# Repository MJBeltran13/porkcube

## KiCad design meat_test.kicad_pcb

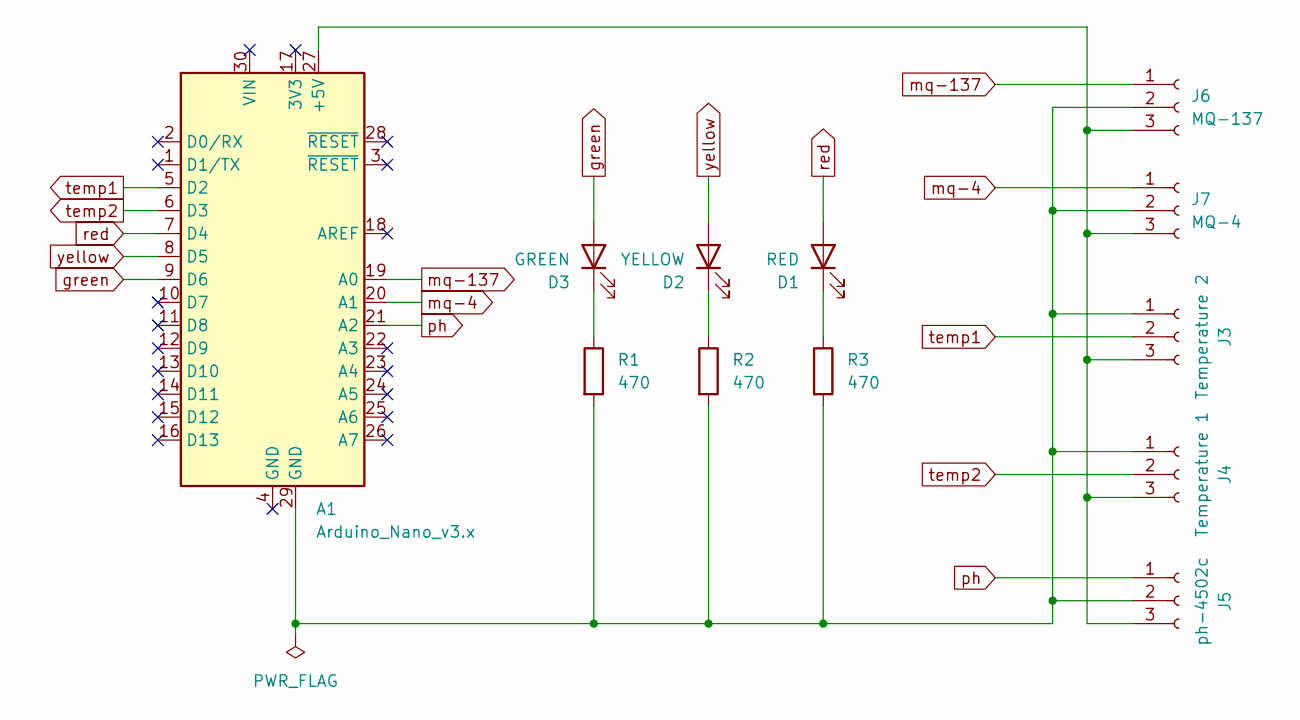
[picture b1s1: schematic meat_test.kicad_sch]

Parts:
A1: Arduino_Nano_v3.x; Arduino_Nano
D1: RED; LED_Rectangular_W3.9mm_H1.8mm_FlatTop
D2: YELLOW; LED_Rectangular_W3.9mm_H1.8mm_FlatTop
D3: GREEN; LED_Rectangular_W3.9mm_H1.8mm_FlatTop
J3: Temperature 2; PinHeader_1x03_P2.54mm_Vertical
J4: Temperature 1; PinHeader_1x03_P2.54mm_Vertical
J5: ph-4502c; PinHeader_1x03_P2.54mm_Vertical
J6: MQ-137; PinHeader_1x03_P2.54mm_Vertical
J7: MQ-4; PinHeader_1x03_P2.54mm_Vertical
R1, R2, R3: 470; R_Axial_DIN0207_L6.3mm_D2.5mm_P10.16mm_Horizontal

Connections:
unnamed: A1.27 (+5V), J3.3, J4.3, J5.3, J6.3, J7.3
unnamed: D1.1 (K), R3.1
unnamed: D2.1 (K), R2.1
unnamed: D3.1 (K), R1.1
unnamed: A1.29 (GND), J3.1, J4.1, J5.2, J6.2, J7.2, R1.2, R2.2, R3.2
green: A1.9 (D6), D3.2 (A)
mq-4: A1.20 (A1), J7.1
mq-137: A1.19 (A0), J6.1
ph: A1.21 (A2), J5.1
red: A1.7 (D4), D1.2 (A)
temp1: A1.5 (D2), J3.2
temp2: A1.6 (D3), J4.2
yellow: A1.8 (D5), D2.2 (A)

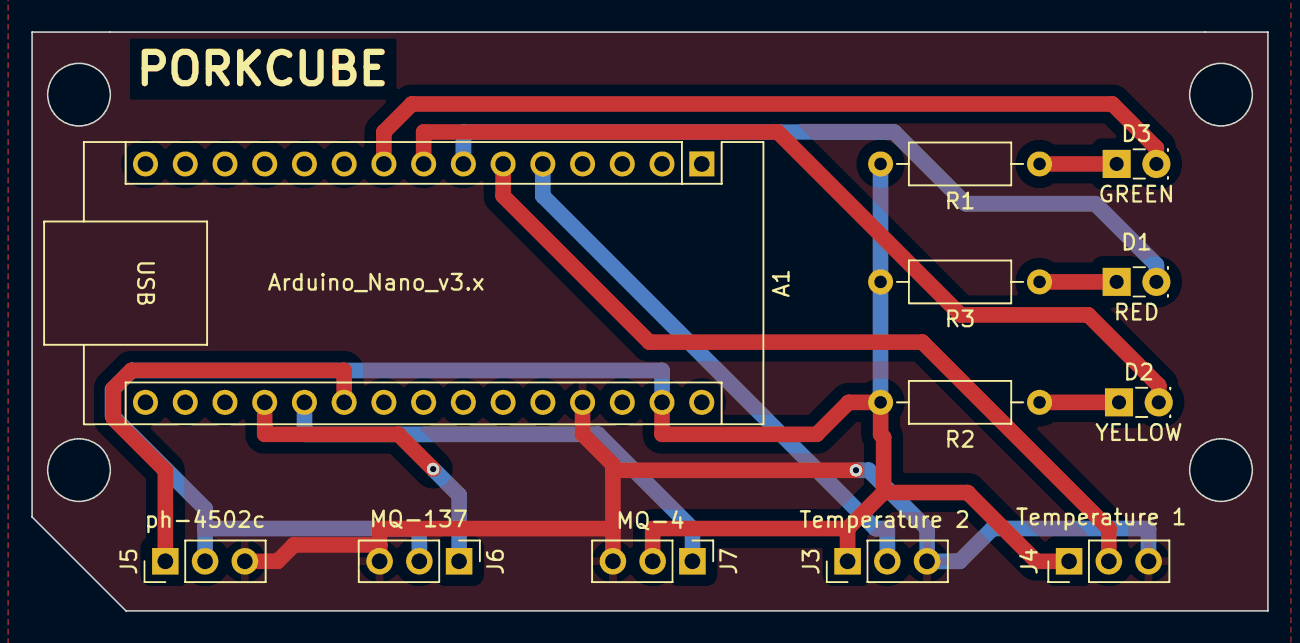
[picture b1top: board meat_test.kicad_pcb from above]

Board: 2 copper layers, 79.0 x 37.0 mm, 12 parts (0 on the bottom side), 13 nets.

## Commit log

2024-03-10 2nd commit
